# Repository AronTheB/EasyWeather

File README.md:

# ESP32 and BME280 based temperature, humidity, and barometric pressure measurer

## Zine

## Description

### Made for [Fallout](https://fallout.hackclub.com/) during a online weekend hackathon

### Why did i make this

I always had this idea, because i never know what to wear outside before leaving my house and I can't be hassled to check the weather app, so i will place this at the door window, so i can look and and check the temperature and other weather stats before leaving.

### How to build

Download the Gerber files and the 3d models and print them out. (I recomend JLCPCB and Prining Leigion). Order all the parts from the BOM section. After everything arrives solder the components togeather with the board and put the PCB in the case and Screw it in with a 2mm Screw. After close the box and screw it in with 3mm Screws. Connect the ESP32 to your computer and flash it with the firmware.

### How to use

After flashing it, turn the ESP32 back on and it should start automaticly. If everything worked out it should start showing the data on the OLED screen.

## KICAD

### Schematic

### PCB layout

### PCB Render (Front/Back)

## FUSION (Front/Back)

## BOM

| NAME | LINK | PRICE | QUANTITY | Need To buy? |
|------|------|-------|----------|--------------|
| XIAO ESP32-S3 | [AliExpress](https://www.aliexpress.com/item/1005007341749305.html) | $10,35 | 1 | Yes |
| BME280 | [AliExpress](https://www.aliexpress.com/item/1005006982994037.html) | $1,82 | 1 | Yes |
| 4,7k Resistors | [AliExpress](https://www.aliexpress.com/item/1005007345052730.html) | $1,36 | 1 | Yes |
| 3D Case | JLC3DP | $2,79 | 1 | Yes |
| PCB | JLCPCB | $5,00 | 1 | Yes |
| **TOTAL** | | **$23,53** | | |

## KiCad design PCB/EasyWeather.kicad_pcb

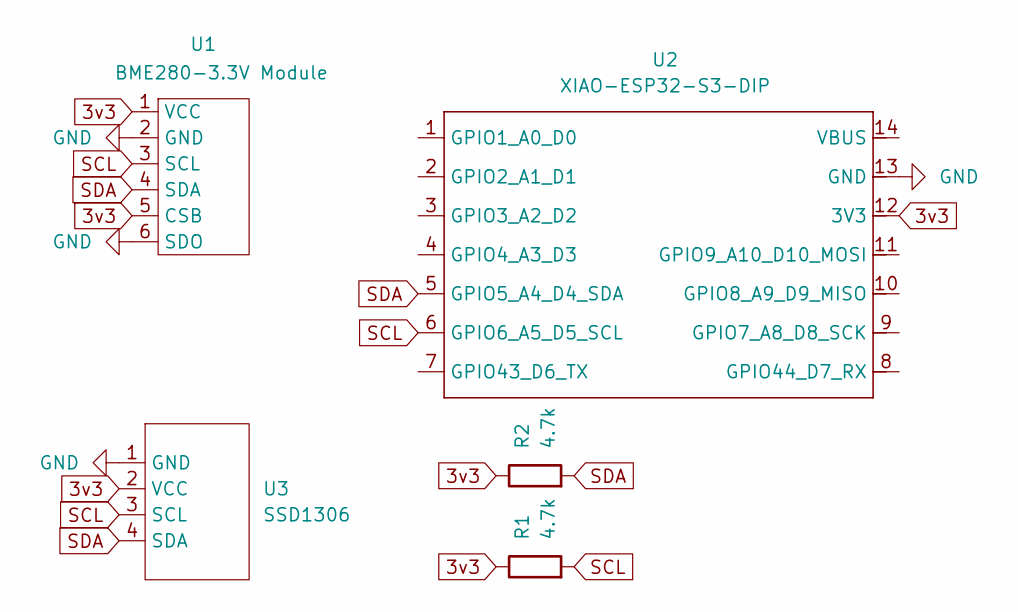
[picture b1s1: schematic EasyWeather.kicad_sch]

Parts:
R1, R2: 4.7k; R_0805_2012Metric_Pad1.20x1.40mm_HandSolder
U1: BME280-3.3V Module; BME280-3.3V
U2: XIAO-ESP32-S3-DIP
U3: SSD1306; 128x64OLED

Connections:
3v3: R1.1, R2.1, U1.1 (VCC), U1.5 (CSB), U2.12 (3V3), U3.2 (VCC)
GND: U1.2 (GND), U1.6 (SDO), U2.13 (GND), U3.1 (GND)
SCL: R1.2, U1.3 (SCL), U2.6 (GPIO6_A5_D5_SCL), U3.3 (SCL)
SDA: R2.2, U1.4 (SDA), U2.5 (GPIO5_A4_D4_SDA), U3.4 (SDA)

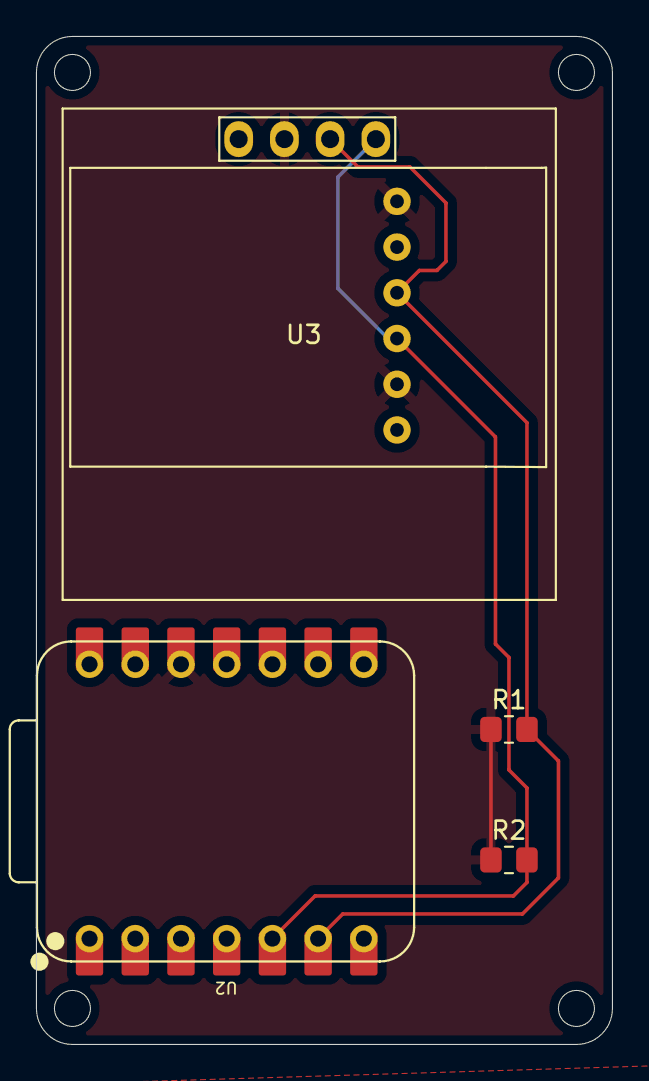
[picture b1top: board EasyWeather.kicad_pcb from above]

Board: 2 copper layers, 32.0 x 56.0 mm, 5 parts (1 on the bottom side), 4 nets.

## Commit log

2026-06-13 moved to PCB folder
2026-06-13 Enhance README with project details and images
    Added detailed project description, including purpose and images of schematic and PCB layout.
2026-06-14 Firmware
2026-06-14 added SSD1306 support
2026-06-14 Revise README for clarity and add build/use instructions
    Updated README to improve clarity and added build instructions.
2026-06-14 Fix formatting of the README header
2026-06-14 Update README for clarity and style
    Corrected capitalization and phrasing in the README.
2026-06-14 Add BOM section to README
    Added a BOM section with components, links, prices, and quantities.
2026-06-14 Add Zine section with image to README
    Added a section for Zine with an image.
2026-06-14 Zine
2026-06-14 new gerber
2026-06-14 Update images and section titles in README
2026-06-14 Rename EasyWeather.csv to BOM.csv
2026-06-14 Rename EsayWeatherBottom.f3z to EasyWeatherBottom.f3z
2026-06-14 Rename EsayWeatherBottom.step to EasyWeatherBottom.step
2026-06-19 Update 3D Case supplier and price in README
2026-06-19 Update BOM.csv with new 3D Case supplier and price
